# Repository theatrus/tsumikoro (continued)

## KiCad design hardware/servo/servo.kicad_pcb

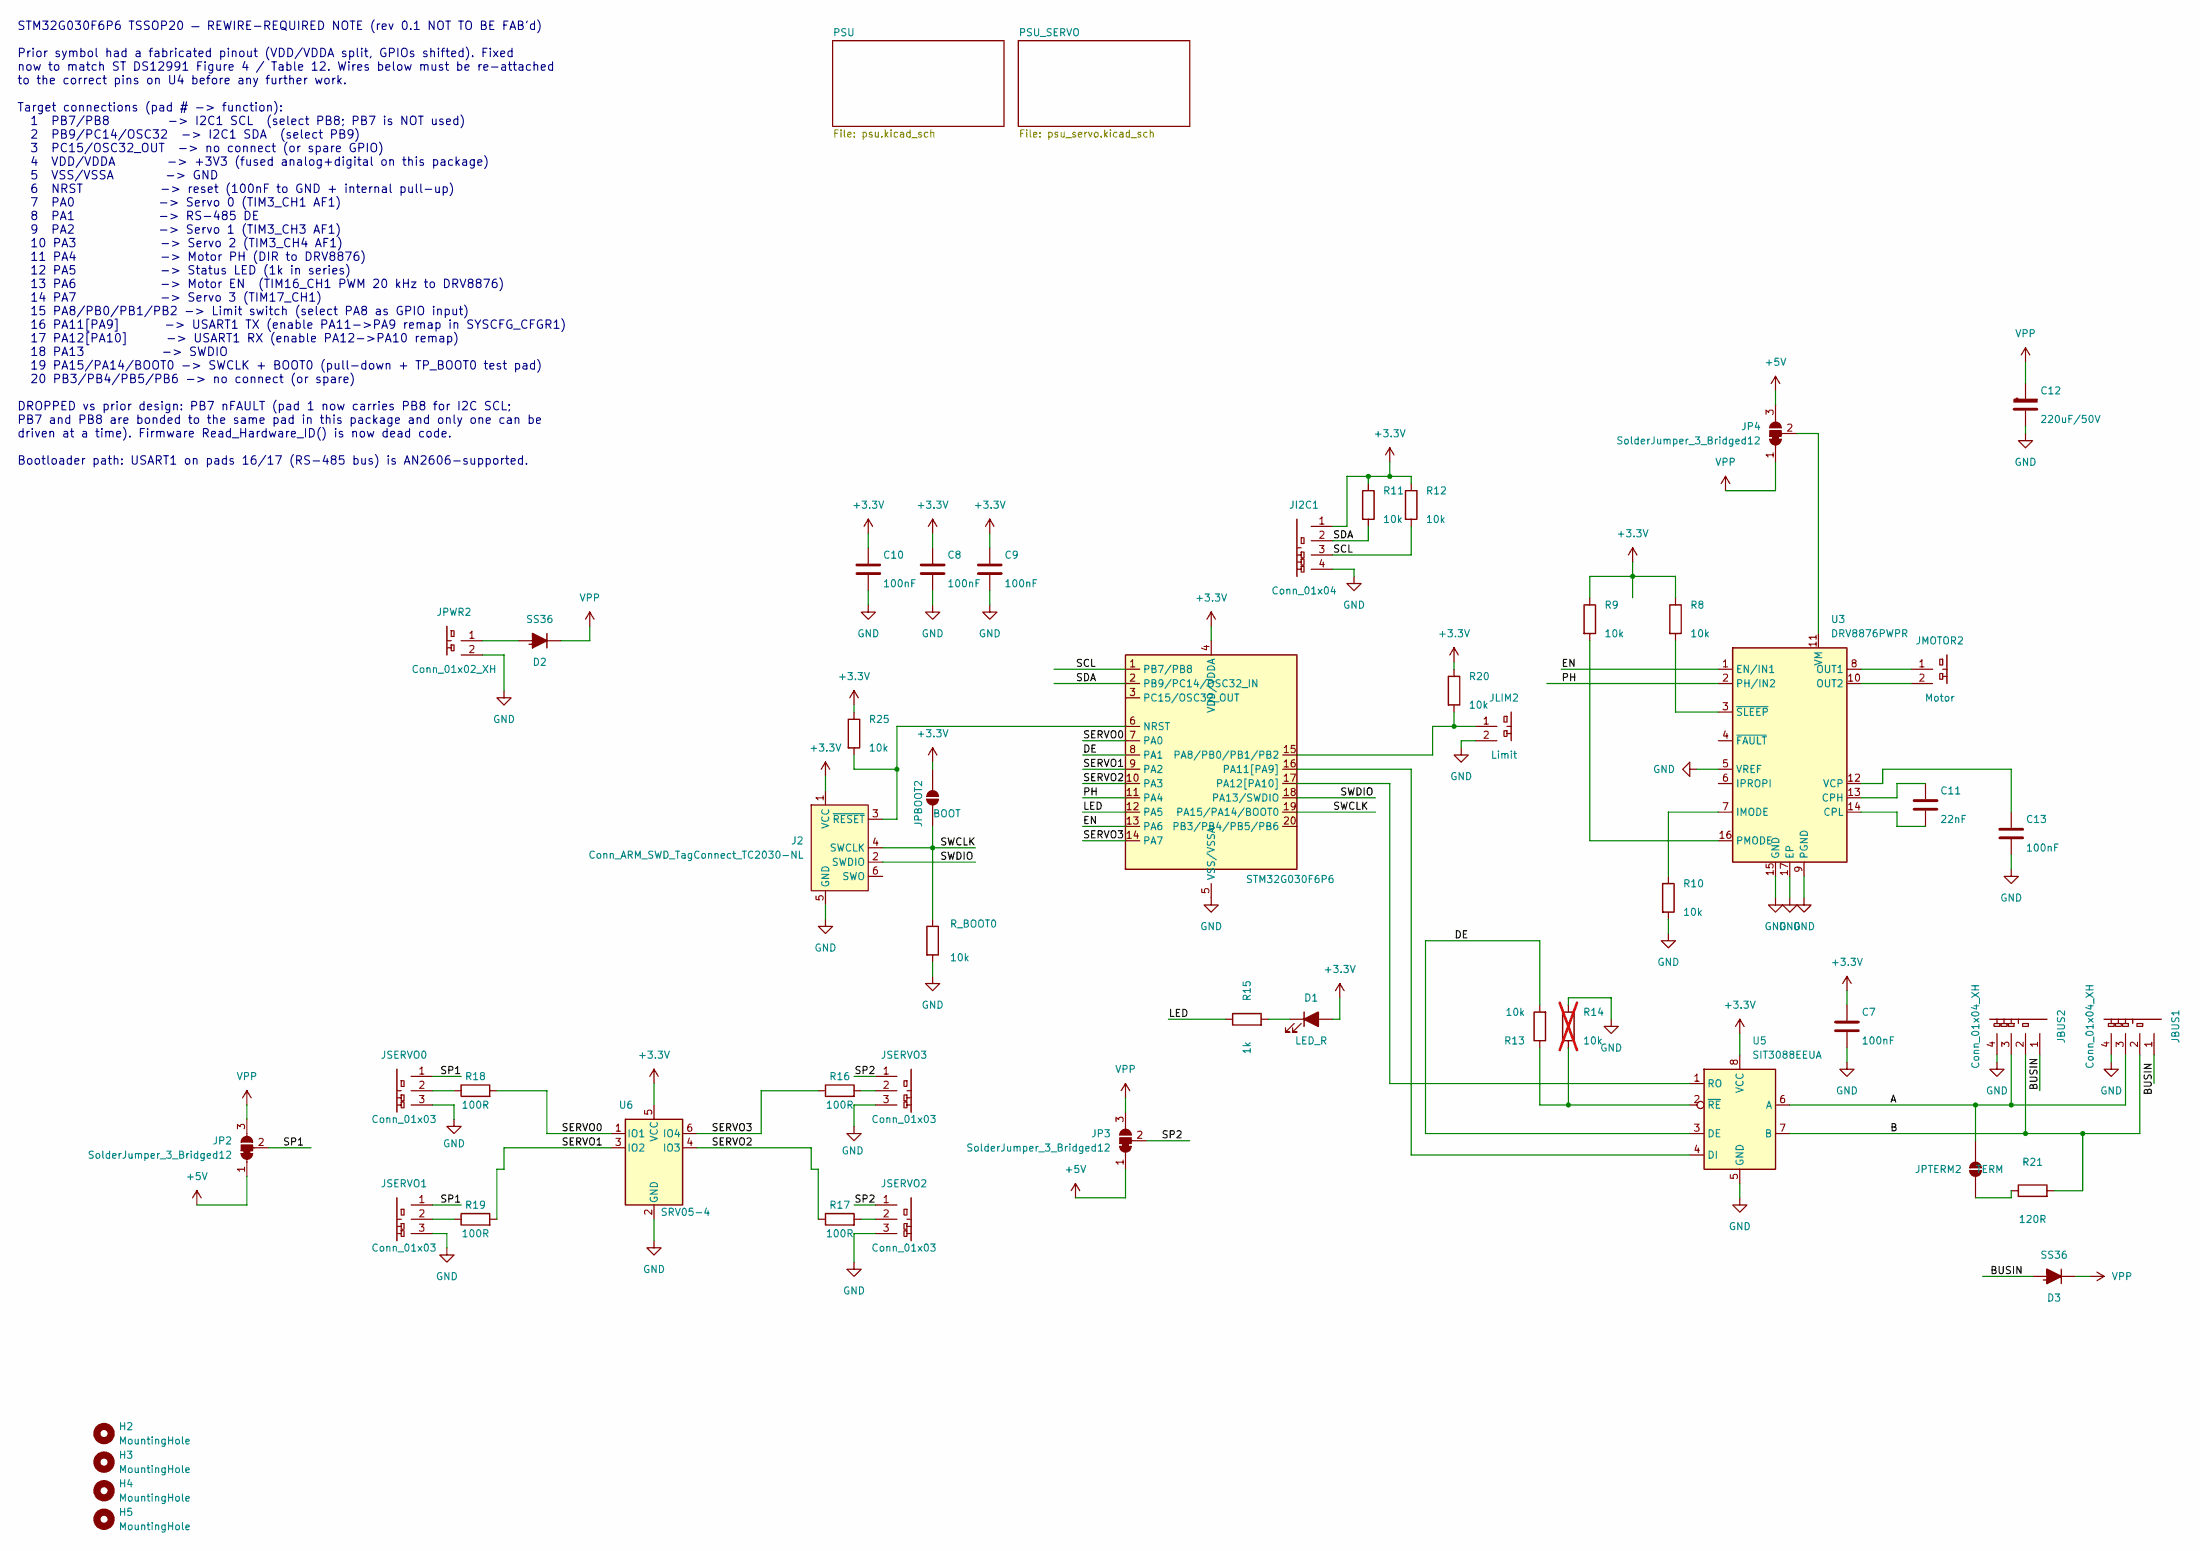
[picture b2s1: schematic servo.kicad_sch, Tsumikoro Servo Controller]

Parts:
C7, C8, C9, C10, C13: 100nF; C_0402_1005Metric; MPN CL05B104KB54PNC; LCSC C307331
C11: 22nF; C_0402_1005Metric; MPN 0402B223K500NT; LCSC C1532
C12: 220uF/50V; CP_Elec_10x10.5; MPN RVT1H221M1010; LCSC C72499
D1: LED_R; LED_0603_1608Metric; MPN KT-0603R; LCSC C2286
D2, D3: SS36; D_SMA; MPN SS36; LCSC C7420367
H2, H3, H4, H5: MountingHole; MountingHole_3.2mm_M3_Pad_TopBottom
J2: Conn_ARM_SWD_TagConnect_TC2030-NL; Tag-Connect_TC2030-IDC-NL_2x03_P1.27mm_Vertical
JBUS1, JBUS2: Conn_01x04_XH; JST_XH_S4B-XH-A_1x04_P2.50mm_Horizontal; MPN S4B-XH-A(LF)(SN); LCSC C157925
JI2C1: Conn_01x04; JST_PH_B4B-PH-K_1x04_P2.00mm_Vertical; MPN B4B-PH-K-S(LF)(SN); LCSC C131334
JLIM2: Limit; JST_PH_B2B-PH-K_1x02_P2.00mm_Vertical; MPN B2B-PH-K-S(LF)(SN); LCSC C131337
JMOTOR2: Motor; JST_PH_B2B-PH-K_1x02_P2.00mm_Vertical; MPN B2B-PH-K-S(LF)(SN); LCSC C131337
JP2, JP3, JP4: SolderJumper_3_Bridged12; SolderJumper-3_P1.3mm_Bridged12_RoundedPad1.0x1.5mm
JPBOOT2: BOOT; SolderJumper-2_P1.3mm_Open_Pad1.0x1.5mm
JPTERM2: TERM
JPWR2: Conn_01x02_XH; JST_XH_S2B-XH-A_1x02_P2.50mm_Horizontal; MPN S2B-XH-A(LF)(SN); LCSC C157931
JSERVO0, JSERVO1, JSERVO2, JSERVO3: Conn_01x03; JST_PH_B3B-PH-K_1x03_P2.00mm_Vertical; MPN B3B-PH-K-S(LF)(SN); LCSC C131339
R8, R9, R10, R11, R12, R13, R20, R25: 10k; R_0402_1005Metric; MPN 0402WGF1002TCE; LCSC C25744
R14: 10k; R_0402_1005Metric; MPN 0402WGF1002TCE; LCSC C25744; not fitted
R15: 1k; R_0402_1005Metric; MPN 0402WGF1001TCE; LCSC C11702
R16, R17, R18, R19: 100R; R_0402_1005Metric; MPN 0402WGF1000TCE; LCSC C25076
R21: 120R; R_1206_3216Metric; MPN RC1206FR-07120RL; LCSC C114928
R_BOOT0: 10k; R_0402_1005Metric; MPN 0402WGF1002TCE; LCSC C25744
U3: DRV8876PWPR; HTSSOP-16-1EP_4.4x5mm_P0.65mm_EP3.4x5mm; MPN DRV8876PWPR; LCSC C575551
U4: STM32G030F6P6; TSSOP-20_4.4x6.5mm_P0.65mm; MPN STM32G030F6P6TR; LCSC C529330
U5: SIT3088EEUA; MSOP-8_3x3mm_P0.65mm; MPN SIT3088EEUA; LCSC C2922535
U6: SRV05-4; SOT-23-6; MPN SRV05-4; LCSC C558418

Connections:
+3.3V: C7.1, C8.1, C9.1, C10.1, D1.2 (A), J2.1 (VCC), JI2C1.1, JPBOOT2.2 (B), R8.1, R9.1, R11.1, R12.1, R20.1, R25.1, U4.4 (VDD/VDDA), U5.8 (VCC), U6.5 (VCC); also elsewhere on the board
+5V: JP2.1 (A), JP3.1 (A), JP4.3 (B); also elsewhere on the board
/<NO NET>: D3.2 (A), JBUS1.1, JBUS2.1
/A: JBUS1.3, JBUS2.3, JPTERM2.2 (B), U5.6 (A)
/B: JBUS1.2, JBUS2.2, R21.2, U5.7 (B)
/DE: R13.2, U4.8 (PA1), U5.3 (DE)
/EN: U3.1 (EN/IN1), U4.13 (PA6)
/LED: R15.1, U4.12 (PA5)
/PH: U3.2 (PH/IN2), U4.11 (PA4)
/SCL: JI2C1.3, R12.2, U4.1 (PB7/PB8)
/SDA: JI2C1.2, R11.2, U4.2 (PB9/PC14/OSC32_IN)
/SERVO0: R18.2, U4.7 (PA0), U6.1 (IO1)
/SERVO1: R19.2, U4.9 (PA2), U6.3 (IO2)
/SERVO2: R17.1, U4.10 (PA3), U6.4 (IO3)
/SERVO3: R16.1, U4.14 (PA7), U6.6 (IO4)
/SP1: JP2.2 (C), JSERVO0.1, JSERVO1.1
/SP2: JP3.2 (C), JSERVO2.1, JSERVO3.1
/SWCLK: J2.4 (SWCLK), JPBOOT2.1 (A), R_BOOT0.1, U4.19 (PA15/PA14/BOOT0)
/SWDIO: J2.2 (SWDIO), U4.18 (PA13/SWDIO)
GND: C7.2, C8.2, C9.2, C10.2, C12.2, C13.2, J2.5 (GND), JBUS1.4, JBUS2.4, JI2C1.4, JLIM2.2, JPWR2.2, JSERVO0.3, JSERVO1.3, JSERVO2.3, JSERVO3.3, R10.2, R14.1, R_BOOT0.2, U3.5 (VREF), U3.9 (PGND), U3.15 (GND), U3.17 (EP), U4.5 (VSS/VSSA), U5.5 (GND), U6.2 (GND); also elsewhere on the board
unnamed: D1.1 (K), R15.2
unnamed: D2.2 (A), JPWR2.1
unnamed: J2.3 (~RESET), R25.2, U4.6 (NRST)
unnamed: JLIM2.1, R20.2, U4.15 (PA8/PB0/PB1/PB2)
unnamed: JMOTOR2.1, U3.8 (OUT1)
unnamed: JMOTOR2.2, U3.10 (OUT2)
unnamed: JP4.2 (C), U3.11 (VM)
unnamed: JPTERM2.1 (A), R21.1
unnamed: JSERVO0.2, R18.1
unnamed: JSERVO1.2, R19.1
unnamed: JSERVO2.2, R17.2
unnamed: JSERVO3.2, R16.2
unnamed: C11.1, U3.13 (CPH)
unnamed: C11.2, U3.14 (CPL)
unnamed: R10.1, U3.7 (IMODE)
unnamed: R9.2, U3.16 (PMODE)
unnamed: C13.1, U3.12 (VCP)
unnamed: R8.2, U3.3 (~SLEEP)
unnamed: U4.16 (PA11[PA9]), U5.4 (DI)
unnamed: U4.17 (PA12[PA10]), U5.1 (RO)
unnamed: R13.1, R14.2, U5.2 (~RE)
VPP: C12.1, D2.1 (K), D3.1 (K), JP2.3 (B), JP3.3 (B), JP4.1 (A); also elsewhere on the board

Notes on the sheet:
STM32G030F6P6 TSSOP20 — REWIRE-REQUIRED NOTE (rev 0.1 NOT TO BE FAB'd) Prior symbol had a fabricated pinout (VDD/VDDA split, GPIOs shifted). Fixed now to match ST DS12991 Figure 4 / Table 12. Wires below must be re-attached to the correct pins on U4 before any further work. Target connections (pad 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

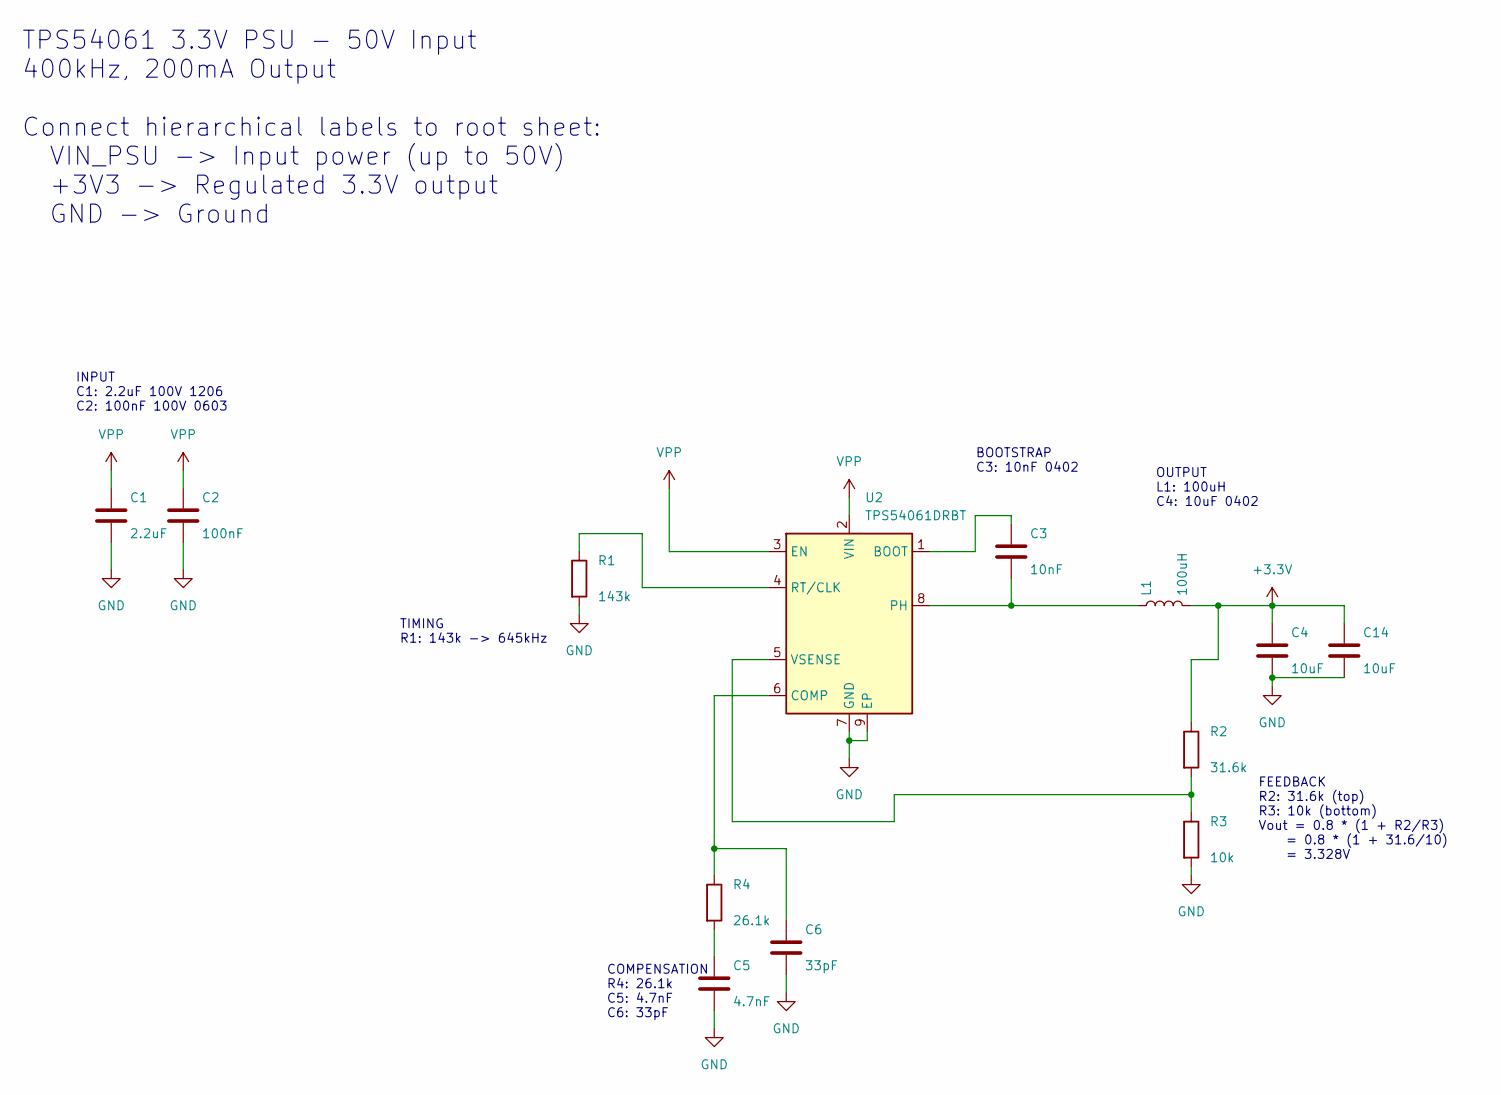
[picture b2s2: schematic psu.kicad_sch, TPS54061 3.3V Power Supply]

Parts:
C1: 2.2uF; C_1206_3216Metric; MPN CL31B225KCHSNNE; LCSC C170101
C2: 100nF; C_0603_1608Metric; MPN CC0603KRX7R0BB104; LCSC C113803
C3: 10nF; C_0402_1005Metric; MPN CL05B103KB5NNNC; LCSC C15195
C4, C14: 10uF; C_0402_1005Metric; MPN CL05A106MP5NUNC; LCSC C315248
C5: 4.7nF; C_0402_1005Metric; MPN 0402B472K500NT; LCSC C1538
C6: 33pF; C_0402_1005Metric; MPN CC0402JRNPO9BN330; LCSC C107005
L1: 100uH; L_Sunlord_SWPA4018S; MPN LVS404018-101M-N; LCSC C142135
R1: 143k; R_0402_1005Metric; MPN 0402WGF1433TCE; LCSC C82292
R2: 31.6k; R_0402_1005Metric; MPN 0402WGF3163TCE; LCSC C25777
R3: 10k; R_0402_1005Metric; MPN 0402WGF1002TCE; LCSC C25744
R4: 26.1k; R_0402_1005Metric; MPN 0402WGF2613TCE; LCSC C27003
U2: TPS54061DRBT; Texas_S-PVSON-N8; MPN TPS54061DRBT; LCSC C2070655

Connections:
+3.3V: C4.1, C14.1, L1.2, R2.1; also elsewhere on the board
GND: C1.2, C2.2, C4.2, C5.2, C6.2, C14.2, R1.2, R3.2, U2.7 (GND), U2.9 (EP); also elsewhere on the board
unnamed: C5.1, R4.2
unnamed: C3.1, U2.1 (BOOT)
unnamed: C6.1, R4.1, U2.6 (COMP)
unnamed: C3.2, L1.1, U2.8 (PH)
unnamed: R1.1, U2.4 (RT/CLK)
unnamed: R2.2, R3.1, U2.5 (VSENSE)
VPP: C1.1, C2.1, U2.2 (VIN), U2.3 (EN); also elsewhere on the board

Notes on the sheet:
TPS54061 3.3V PSU - 50V Input 400kHz, 200mA Output Connect hierarchical labels to root sheet: VIN_PSU -> Input power (up to 50V) +3V3 -> Regulated 3.3V output GND -> Ground
COMPENSATION R4: 26.1k C5: 4.7nF C6: 33pF
OUTPUT L1: 100uH C4: 10uF 0402
TIMING R1: 143k -> 645kHz
INPUT C1: 2.2uF 100V 1206 C2: 100nF 100V 0603
FEEDBACK R2: 31.6k (top) R3: 10k (bottom) Vout = 0.8 * (1 + R2/R3) = 0.8 * (1 + 31.6/10) = 3.328V
BOOTSTRAP C3: 10nF 0402

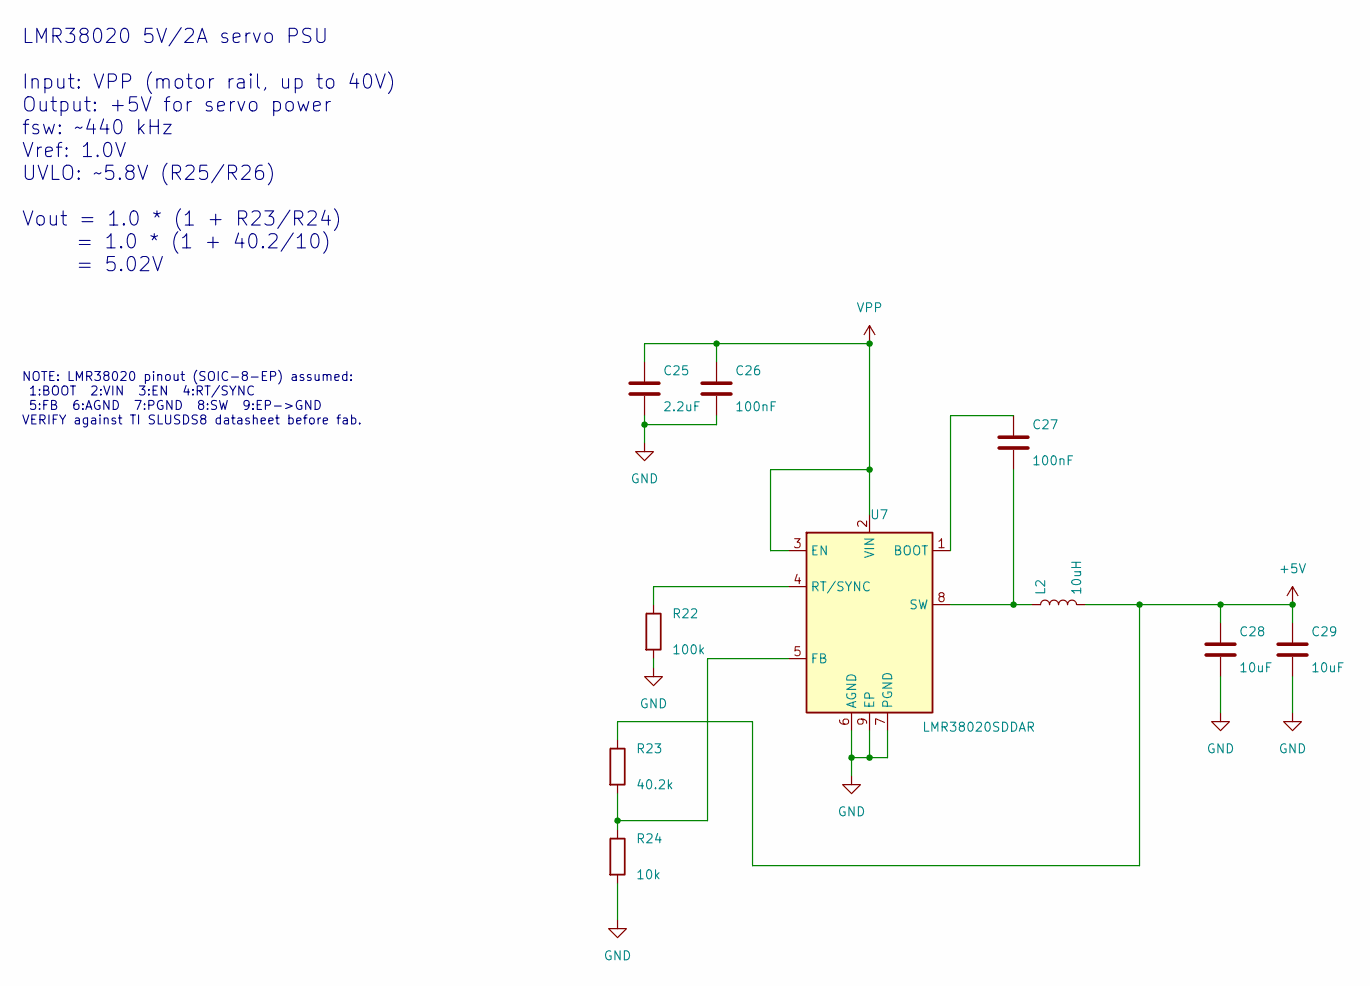
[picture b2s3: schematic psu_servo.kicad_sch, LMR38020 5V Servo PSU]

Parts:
C25: 2.2uF; C_1206_3216Metric; MPN CL31B225KCHSNNE; LCSC C170101
C26: 100nF; C_0603_1608Metric; MPN CC0603KRX7R0BB104; LCSC C113803
C27: 100nF; C_0402_1005Metric; MPN CL05B104KB54PNC; LCSC C307331
C28, C29: 10uF; C_0805_2012Metric; MPN CL21A106KAYNNNE; LCSC C15850
L2: 10uH; L_Changjiang_FNR4030S; MPN FNR4030S100MT; LCSC C167879
R22: 100k; R_0402_1005Metric; MPN 0402WGF1003TCE; LCSC C25741
R23: 40.2k; R_0402_1005Metric; MPN 0402WGF4022TCE; LCSC C25893
R24: 10k; R_0402_1005Metric; MPN 0402WGF1002TCE; LCSC C25744
U7: LMR38020SDDAR; SOIC-8-1EP_3.9x4.9mm_P1.27mm_EP2.29x3mm; MPN LMR38020SDDAR; LCSC C3192337

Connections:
+5V: C28.1, C29.1, L2.2, R23.1; also elsewhere on the board
GND: C25.2, C26.2, C28.2, C29.2, R22.2, R24.2, U7.6 (AGND), U7.7 (PGND), U7.9 (EP); also elsewhere on the board
unnamed: C27.1, U7.1 (BOOT)
unnamed: R23.2, R24.1, U7.5 (FB)
unnamed: R22.1, U7.4 (RT/SYNC)
unnamed: C27.2, L2.1, U7.8 (SW)
VPP: C25.1, C26.1, U7.2 (VIN), U7.3 (EN); also elsewhere on the board

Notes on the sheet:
LMR38020 5V/2A servo PSU Input: VPP (motor rail, up to 40V) Output: +5V for servo power fsw: ~440 kHz Vref: 1.0V UVLO: ~5.8V (R25/R26) Vout = 1.0 * (1 + R23/R24) = 1.0 * (1 + 40.2/10) = 5.02V
NOTE: LMR38020 pinout (SOIC-8-EP) assumed: 1:BOOT 2:VIN 3:EN 4:RT/SYNC 5:FB 6:AGND 7:PGND 8:SW 9:EP->GND VERIFY against TI SLUSDS8 datasheet before fab.

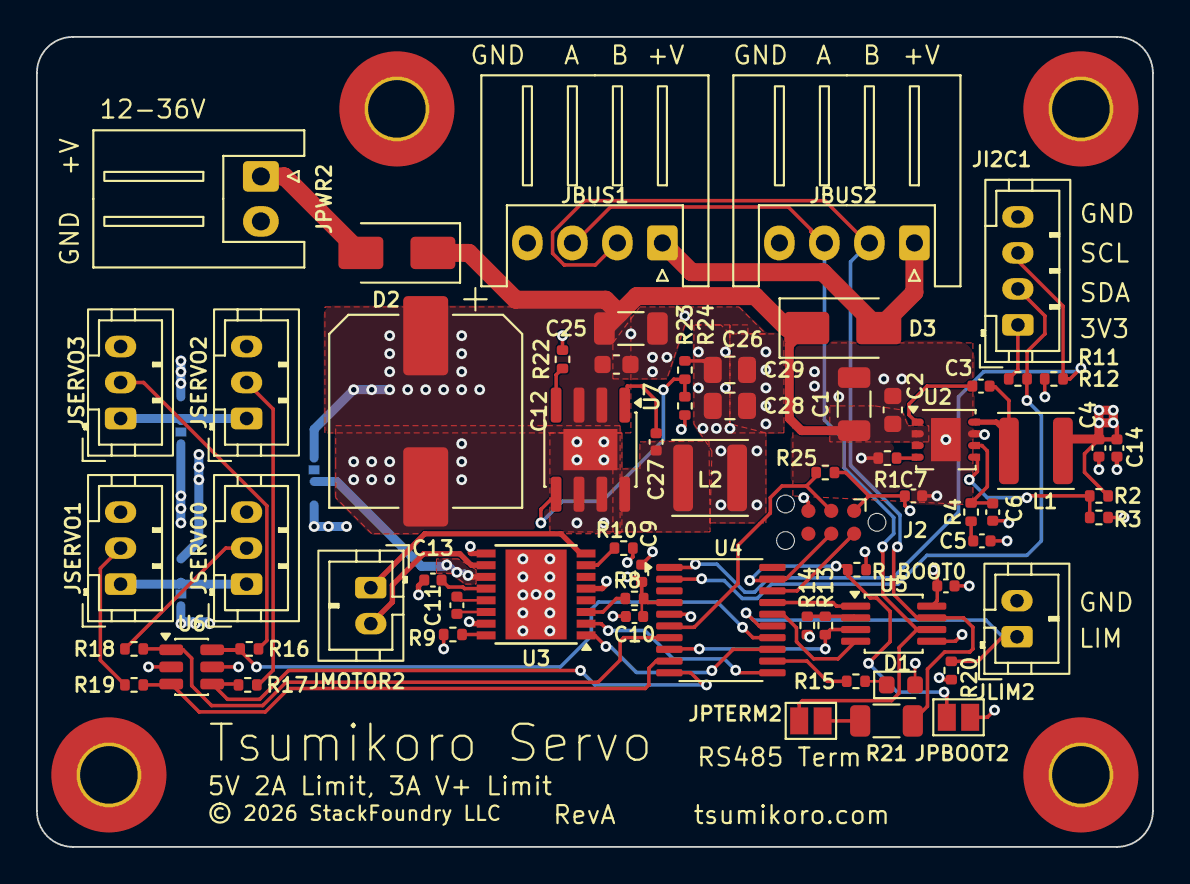
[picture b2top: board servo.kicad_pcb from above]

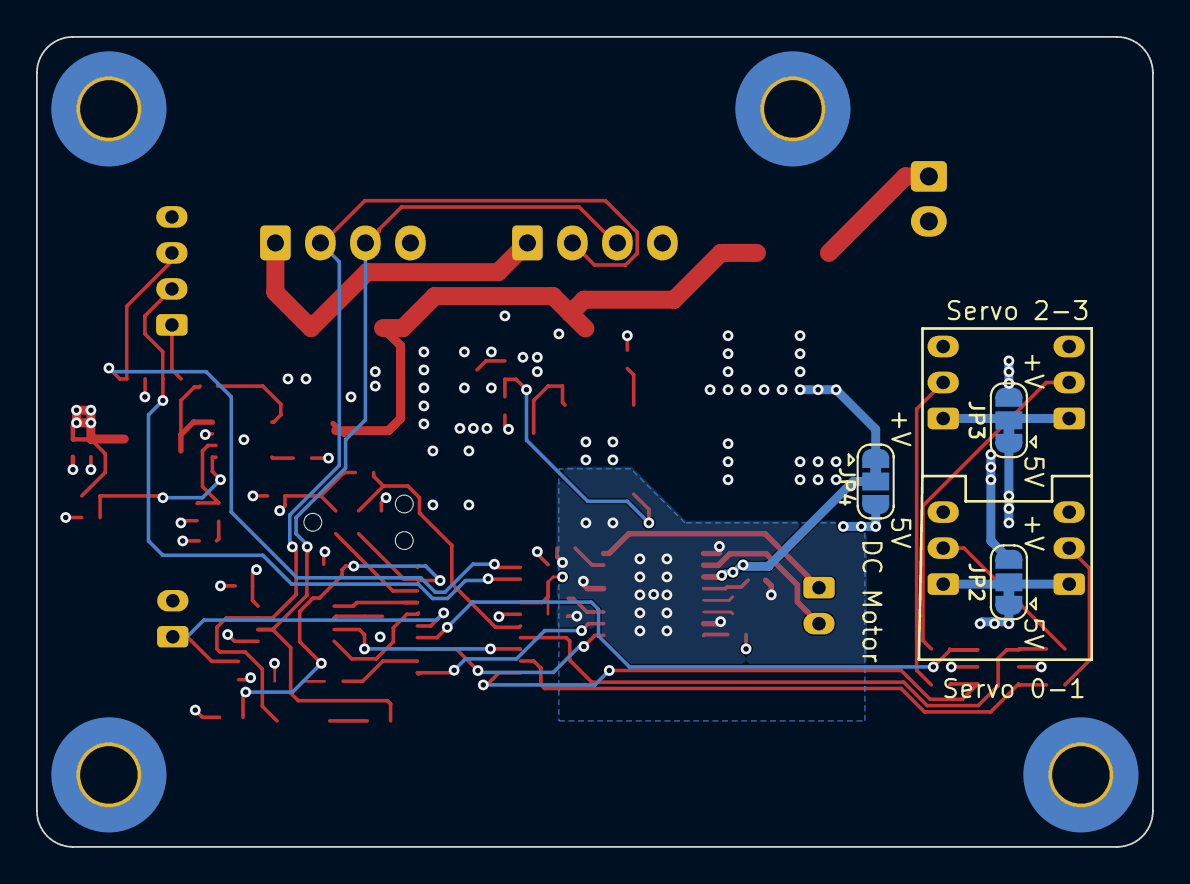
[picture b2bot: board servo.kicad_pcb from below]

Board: 4 copper layers, 62.0 x 45.0 mm, 73 parts (3 on the bottom side), 52 nets.

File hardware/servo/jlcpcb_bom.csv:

"Item","Designator","Comment","Footprint","Qty","LCSC Part #","MPN","Manufacturer"
"1","C1,C25","2.2uF","Capacitor_SMD:C_1206_3216Metric","2","C170101","CL31B225KCHSNNE","Samsung"
"2","C2,C26","100nF","Capacitor_SMD:C_0603_1608Metric","2","C113803","CC0603KRX7R0BB104","Yageo"
"3","C3","10nF","Capacitor_SMD:C_0402_1005Metric","1","C15195","CL05B103KB5NNNC","Samsung"
"4","C4,C14","10uF","Capacitor_SMD:C_0402_1005Metric","2","C315248","CL05A106MP5NUNC","Samsung"
"5","C5","4.7nF","Capacitor_SMD:C_0402_1005Metric","1","C1538","0402B472K500NT","FH"
"6","C6","33pF","Capacitor_SMD:C_0402_1005Metric","1","C107005","CC0402JRNPO9BN330","Yageo"
"7","C7-C10,C13,C27","100nF","Capacitor_SMD:C_0402_1005Metric","6","C307331","CL05B104KB54PNC","Samsung"
"8","C11","22nF","Capacitor_SMD:C_0402_1005Metric","1","C1532","0402B223K500NT","FH"
"9","C12","220uF/50V","Capacitor_SMD:CP_Elec_10x10.5","1","C72499","RVT1H221M1010","Lelon"
"10","C28,C29","10uF","Capacitor_SMD:C_0805_2012Metric","2","C15850","CL21A106KAYNNNE","Samsung"
"11","D1","LED_R","LED_SMD:LED_0603_1608Metric","1","C2286","KT-0603R","Hubei KENTO Elec"
"12","D2,D3","SS36","Diode_SMD:D_SMA","2","C7420367","SS36","Multiple"
"13","JBUS1,JBUS2","Conn_01x04_XH","Connector_JST:JST_XH_S4B-XH-A_1x04_P2.50mm_Horizontal","2","C157925","S4B-XH-A(LF)(SN)","JST"
"14","JI2C1","Conn_01x04","Connector_JST:JST_PH_B4B-PH-K_1x04_P2.00mm_Vertical","1","C131334","B4B-PH-K-S(LF)(SN)","JST"
"15","JLIM2","Limit","Connector_JST:JST_PH_B2B-PH-K_1x02_P2.00mm_Vertical","1","C131337","B2B-PH-K-S(LF)(SN)","JST"
"16","JMOTOR2","Motor","Connector_JST:JST_PH_B2B-PH-K_1x02_P2.00mm_Vertical","1","C131337","B2B-PH-K-S(LF)(SN)","JST"
"17","JPWR2","Conn_01x02_XH","Connector_JST:JST_XH_S2B-XH-A_1x02_P2.50mm_Horizontal","1","C157931","S2B-XH-A(LF)(SN)","JST"
"18","JSERVO0-JSERVO3","Conn_01x03","Connector_JST:JST_PH_B3B-PH-K_1x03_P2.00mm_Vertical","4","C131339","B3B-PH-K-S(LF)(SN)","JST"
"19","L1","100uH","Inductor_SMD:L_Sunlord_SWPA4018S","1","C142135","LVS404018-101M-N","BOURNS/LVS"
"20","L2","10uH","Inductor_SMD:L_Changjiang_FNR4030S","1","C167879","FNR4030S100MT","Sunlord"
"21","R1","143k","Resistor_SMD:R_0402_1005Metric","1","C82292","0402WGF1433TCE","UNI-ROYAL"
"22","R2","31.6k","Resistor_SMD:R_0402_1005Metric","1","C25777","0402WGF3163TCE","UNI-ROYAL"
"23","R3,R8-R13,R20,R24,R25,R_BOOT0","10k","Resistor_SMD:R_0402_1005Metric","11","C25744","0402WGF1002TCE","UNI-ROYAL"
"24","R4","26.1k","Resistor_SMD:R_0402_1005Metric","1","C27003","0402WGF2613TCE","UNI-ROYAL"
"25","R15","1k","Resistor_SMD:R_0402_1005Metric","1","C11702","0402WGF1001TCE","UNI-ROYAL"
"26","R16-R19","100R","Resistor_SMD:R_0402_1005Metric","4","C25076","0402WGF1000TCE","UNI-ROYAL"
"27","R21","120R","Resistor_SMD:R_1206_3216Metric","1","C114928","RC1206FR-07120RL","Yageo"
"28","R22","100k","Resistor_SMD:R_0402_1005Metric","1","C25741","0402WGF1003TCE","UNI-ROYAL"
"29","R23","40.2k","Resistor_SMD:R_0402_1005Metric","1","C25893","0402WGF4022TCE","UNI-ROYAL"
"30","U2","TPS54061DRBT","Package_SON:Texas_S-PVSON-N8","1","C2070655","TPS54061DRBT",""
"31","U3","DRV8876PWPR","Package_SO:HTSSOP-16-1EP_4.4x5mm_P0.65mm_EP3.4x5mm","1","C575551","DRV8876PWPR",""
"32","U4","STM32G030F6P6","Package_SO:TSSOP-20_4.4x6.5mm_P0.65mm","1","C529330","STM32G030F6P6TR",""
"33","U5","SIT3088EEUA","Package_SO:MSOP-8_3x3mm_P0.65mm","1","C2922535","SIT3088EEUA",""
"34","U6","SRV05-4","Package_TO_SOT_SMD:SOT-23-6","1","C558418","SRV05-4","Littelfuse"
"35","U7","LMR38020SDDAR","Package_SO:SOIC-8-1EP_3.9x4.9mm_P1.27mm_EP2.29x3mm","1","C3192337","LMR38020SDDAR","Texas Instruments"

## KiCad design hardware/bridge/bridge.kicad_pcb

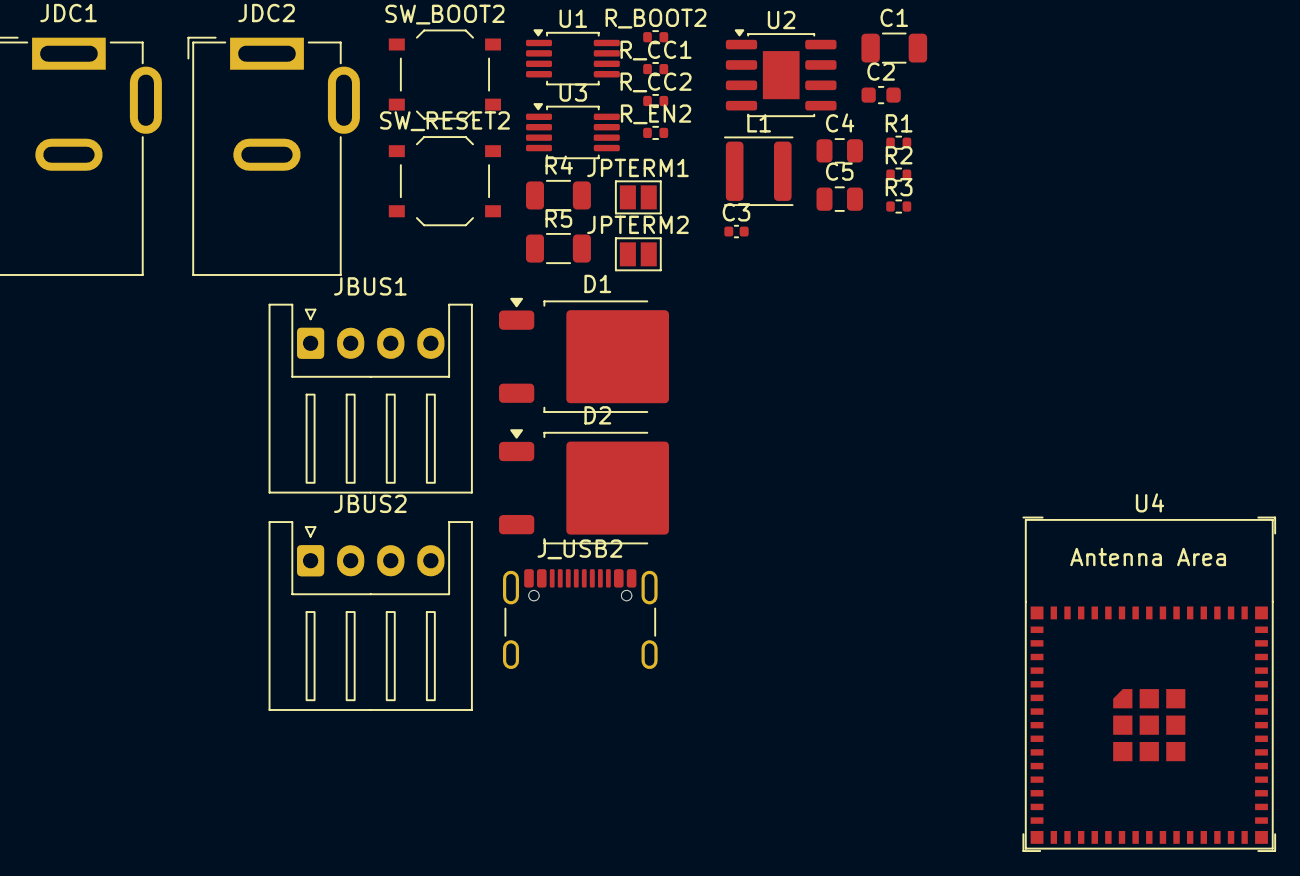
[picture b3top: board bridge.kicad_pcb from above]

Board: 4 copper layers, 30 parts (0 on the bottom side), 3 nets, no tracks yet.

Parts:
C1: 2.2uF; C_1206_3216Metric
C2: 100nF; C_0603_1608Metric
C3: 100nF; C_0402_1005Metric
C4, C5: 10uF; C_0805_2012Metric
D1, D2: MBRD10200; TO-252-2
JBUS1, JBUS2: Conn_01x04_XH; JST_XH_S4B-XH-A_1x04_P2.50mm_Horizontal
JDC1, JDC2: DC-005 2.0mm; BarrelJack_GCT_DCJ200-10-A_Horizontal
JPTERM1: TERM1; SolderJumper-2_P1.3mm_Open_Pad1.0x1.5mm
JPTERM2: TERM2; SolderJumper-2_P1.3mm_Open_Pad1.0x1.5mm
J_USB2: USB-TYPE-C-019; USB_C_Receptacle_GCT_USB4105-xx-A_16P_TopMnt_Horizontal
L1: 10uH; L_Changjiang_FNR4030S
R1: 100k; R_0402_1005Metric
R2: 22k; R_0402_1005Metric
R3: 10k; R_0402_1005Metric
R4, R5: 120R; R_1206_3216Metric
R_BOOT2: 10k; R_0402_1005Metric
R_CC1, R_CC2: 5.1k; R_0402_1005Metric
R_EN2: 10k; R_0402_1005Metric
SW_BOOT2: BOOT; SW_Push_1P1T_XKB_TS-1187A
SW_RESET2: RESET; SW_Push_1P1T_XKB_TS-1187A
U1, U3: SIT3088EEUA; MSOP-8_3x3mm_P0.65mm
U2: LMR38020SDDAR; SOIC-8-1EP_3.9x4.9mm_P1.27mm_EP2.29x3mm
U4: ESP32-S3-MINI-1-N8; ESP32-S3-MINI-1

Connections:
unnamed: J_USB2.A1 (GND), J_USB2.A12 (GND), J_USB2.B1 (GND), J_USB2.B12 (GND)
unnamed: J_USB2.A4 (VBUS), J_USB2.A9 (VBUS), J_USB2.B4 (VBUS), J_USB2.B9 (VBUS)
unnamed: U4.1 (GND), U4.2 (GND), U4.42 (GND), U4.43 (GND), U4.46 (GND), U4.47 (GND), U4.48 (GND), U4.49 (GND), U4.50 (GND), U4.51 (GND), U4.52 (GND), U4.53 (GND), U4.54 (GND), U4.55 (GND), U4.56 (GND), U4.57 (GND), U4.58 (GND), U4.59 (GND), U4.60 (GND), U4.61 (GND), U4.62 (GND), U4.63 (GND), U4.64 (GND), U4.65 (GND)

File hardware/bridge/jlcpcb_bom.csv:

"Item","Designator","Comment","Footprint","Qty","LCSC Part #","MPN","Manufacturer"
"1","C1","2.2uF","Capacitor_SMD:C_1206_3216Metric","1","C170101","CL31B225KCHSNNE","Samsung"
"2","C2","100nF","Capacitor_SMD:C_0603_1608Metric","1","C113803","CC0603KRX7R0BB104","Yageo"
"3","C3","100nF","Capacitor_SMD:C_0402_1005Metric","1","C1525","CL05B104KO5NNNC","Samsung"
"4","C4,C5","10uF","Capacitor_SMD:C_0805_2012Metric","2","C15850","CL21A106KAYNNNE","Samsung"
"5","D1,D2","MBRD10200","Package_TO_SOT_SMD:TO-252-2","2","C260297","MBRD10200","onsemi"
"6","JBUS1,JBUS2","Conn_01x04_XH","Connector_JST:JST_XH_S4B-XH-A_1x04_P2.50mm_Horizontal","2","C157925","S4B-XH-A(LF)(SN)","JST"
"7","JDC1,JDC2","DC-005 2.0mm","Connector_BarrelJack:BarrelJack_CUI_PJ-063AH_Horizontal","2","C2880546","DC-005K-5A-2.0","XKB Connectivity"
"8","JPTERM1","TERM1","Jumper:SolderJumper-2_P1.3mm_Open_Pad1.0x1.5mm","1","","",""
"9","JPTERM2","TERM2","Jumper:SolderJumper-2_P1.3mm_Open_Pad1.0x1.5mm","1","","",""
"10","J_ESP_L?","ESP32-L 1x19","Connector_PinHeader_2.54mm:PinSocket_1x19_P2.54mm_Vertical","1","","",""
"11","J_ESP_R?","ESP32-R 1x19","Connector_PinHeader_2.54mm:PinSocket_1x19_P2.54mm_Vertical","1","","",""
"12","L1","10uH","Inductor_SMD:L_Changjiang_FNR4030S","1","C167879","FNR4030S100MT","Sunlord"
"13","R1","100k","Resistor_SMD:R_0402_1005Metric","1","C25741","0402WGF1003TCE","UNI-ROYAL"
"14","R2","22k","Resistor_SMD:R_0402_1005Metric","1","C25768","0402WGF2202TCE","UNI-ROYAL"
"15","R3","10k","Resistor_SMD:R_0402_1005Metric","1","C25744","0402WGF1002TCE","UNI-ROYAL"
"16","R4,R5","120R","Resistor_SMD:R_1206_3216Metric","2","C114928","RC1206FR-07120RL","Yageo"
"17","U1,U3","SIT3088EEUA","Package_SO:MSOP-8_3x3mm_P0.65mm","2","C2922535","SIT3088EEUA","3PEAK"
"18","U2","LMR38020SDDAR","Package_SO:SOIC-8-1EP_3.9x4.9mm_P1.27mm_EP2.29x3mm","1","C3192337","LMR38020SDDAR","Texas Instruments"

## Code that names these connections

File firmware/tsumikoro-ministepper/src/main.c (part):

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 * the `PIN_*` defines below MUST stay in sync with that document.
 *
 * Peripheral allocation:
 *   USART2 (PA2/PA3)          - RS-485 bus @ 1 Mbaud
 *   SPI1   (PA5/PA6/PA7)      - shared SPI to both TMC2130s
 *   TIM1_CH1 (PA8)            - STEP1 pulse generator
 *   TIM2_CH1 (PA0)            - STEP2 pulse generator
 *   I2C1   (PB6/PB7)          - expansion bus (AF6)
 *
 * USART2 is used instead of USART1 to avoid the PA11/PA12 vs PA9/PA10
 * shared-pad trap that hit the servo firmware on STM32G030F6P6 — on
 * the G071 UFQFPN-28 PA2/PA3 are dedicated pins so no SYSCFG remap is
 * needed.
 */

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#define PIN_TMC1_CS_PORT        GPIOA
#define PIN_TMC1_CS             GPIO_PIN_4   /* pin 10 - CS1 */
#define PIN_TMC1_STEP_PORT      GPIOA
#define PIN_TMC1_STEP           GPIO_PIN_8   /* pin 16 - STEP1 (TIM1_CH1, AF2) */
#define PIN_TMC1_DIR_PORT       GPIOA
#define PIN_TMC1_DIR            GPIO_PIN_15  /* pin 22 - DIR1 */
#define PIN_TMC1_DIAG_PORT      GPIOB
#define PIN_TMC1_DIAG           GPIO_PIN_1   /* pin 15 - DIAG1 (open-drain + 47k pull-up) */

/* TMC2130 driver 2 (U3) - axis 2 */
#define PIN_TMC2_CS_PORT        GPIOA
#define PIN_TMC2_CS             GPIO_PIN_9   /* pin 19 - CS2 (was PA12, moved for USB) */
#define PIN_TMC2_STEP_PORT      GPIOA
#define PIN_TMC2_STEP           GPIO_PIN_0   /* pin 6  - STEP2 (TIM2_CH1, AF2) */
#define PIN_TMC2_DIR_PORT       GPIOC        /* <-- PC6 (pin 17); PB2 is not bonded out on UFQFPN28 */
#define PIN_TMC2_DIR            GPIO_PIN_6   /* pin 17 - DIR2 */
#define PIN_TMC2_DIAG_PORT      GPIOB
#define PIN_TMC2_DIAG           GPIO_PIN_4   /* pin 24 - DIAG2 */

/* Shared DRV_ENN for both TMC2130s (active-low enable) */
#define PIN_DRV_ENN_PORT        GPIOB
#define PIN_DRV_ENN             GPIO_PIN_2   /* pin 17 - active low enable (was PA11, moved for USB) */

/* Per-axis limit / home switches */
#define PIN_LIMIT1_PORT         GPIOB
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#define PIN_I2C_SCL             GPIO_PIN_6   /* pin 26 - I2C1 SCL (AF6) */
#define PIN_I2C_SDA             GPIO_PIN_7   /* pin 27 - I2C1 SDA (AF6) */

/* USB (PA11=D-, PA12=D+ on UFQFPN-32 pins 22/23) — handled by USB peripheral, not GPIO */
/* Spares on UFQFPN32: PB9 (pin 1), PC14 (pin 2), PC15 (pin 3), PA10 (pin 21), PB8 (pin 32) */

/* ===== Task sizes ======================================================== */

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{
    __HAL_RCC_GPIOA_CLK_ENABLE();
    __HAL_RCC_GPIOB_CLK_ENABLE();
    __HAL_RCC_GPIOC_CLK_ENABLE();   /* PC6 = DIR2 */

    GPIO_InitTypeDef gpio = {0};

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    gpio.Speed = GPIO_SPEED_FREQ_LOW;
    HAL_GPIO_Init(PIN_LED_PORT, &gpio);

    /* USART2 AF1 on PA2/PA3 (pins 6/7) */
    gpio.Pin = PIN_UART_TX | PIN_UART_RX;
    gpio.Mode = GPIO_MODE_AF_PP;
    gpio.Pull = GPIO_PULLUP;
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    gpio.Alternate = GPIO_AF1_USART2;
    HAL_GPIO_Init(PIN_UART_PORT, &gpio);

    /* RS-485 DE on PA1 - the HAL module manages this pin explicitly */
    gpio.Pin = PIN_DE;
    gpio.Mode = GPIO_MODE_OUTPUT_PP;
    gpio.Pull = GPIO_NOPULL;
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    HAL_GPIO_Init(PIN_DE_PORT, &gpio);
    HAL_GPIO_WritePin(PIN_DE_PORT, PIN_DE, GPIO_PIN_RESET);  /* start in RX */

    /* TMC1 CS (PA4), TMC2 CS (PA12), DRV_ENN (PA11), DIR1 (PA15) — all GPIO outputs.
     * Hold CS high (inactive) and DRV_ENN high (outputs disabled) at boot. */
    gpio.Pin = PIN_TMC1_CS | PIN_TMC2_CS | PIN_DRV_ENN;
    gpio.Mode = GPIO_MODE_OUTPUT_PP;
    gpio.Pull = GPIO_NOPULL;
    gpio.Speed = GPIO_SPEED_FREQ_MEDIUM;
    HAL_GPIO_Init(GPIOA, &gpio);
    HAL_GPIO_WritePin(GPIOA, PIN_TMC1_CS | PIN_TMC2_CS, GPIO_PIN_SET);
    HAL_GPIO_WritePin(PIN_DRV_ENN_PORT, PIN_DRV_ENN, GPIO_PIN_SET);  /* drivers off */

    gpio.Pin = PIN_TMC1_DIR;
    HAL_GPIO_Init(PIN_TMC1_DIR_PORT, &gpio);
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    gpio.Pin = PIN_LIMIT2;
    HAL_GPIO_Init(PIN_LIMIT2_PORT, &gpio);

    /* STEP1 (PA8) will be configured as TIM1_CH1 AF2 by Stepper_Init.
     * STEP2 (PA0) will be configured as TIM2_CH1 AF2 by Stepper_Init.
     * SPI1 (PA5/6/7) will be configured when the SPI driver is added. */
}

static void UART_Init(void)
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static void Stepper_Init(void)
{
    /* TODO:
     *  - Configure SPI1 on PA5/6/7 (AF0) for shared TMC2130 bus
     *  - Configure TIM1_CH1 (PA8) and TIM2_CH1 (PA0) for STEP pulse
     *    generation (one-pulse mode or free-running with DMA-driven ARR)
     *  - Reset TMC2130s (hold DRV_ENN, write GCONF/CHOPCONF/IHOLD_IRUN
     *    via SPI)
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
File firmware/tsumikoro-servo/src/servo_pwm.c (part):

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{
    /* Initialize servo channels with configuration
     * Pin mapping (STM32G030F6P6 TSSOP20, servo PCB rev 0.1):
     * Channel 0: PA0 - TIM3_CH1  (AF1)
     * Channel 1: PA2 - TIM3_CH3  (AF1)
     * Channel 2: PA3 - TIM3_CH4  (AF1)
     * Channel 3: PA7 - TIM17_CH1 (AF5)
     *
     * Former servo channels now reassigned for motor control / I2C / fault:
     * - PA4 (was Servo 3, TIM14_CH1) -> DRV8876 PH pin (direction)
     * - PA6 (was Servo 4, TIM16_CH1) -> DRV8876 EN pin (PWM, via TIM16_CH1)
     * - PA7 (was Servo 5)            -> now Servo 3 on this channel
     *
     * Protected / reserved pins:
     * - PA13, PA14: SWD (SWDIO, SWCLK) - DO NOT USE
     * - PA9,  PA10: USART1 for RS-485 bus (requires SYSCFG remap on TSSOP20)
     * - PA1:        RS-485 DE
     * - PA5:        Status LED
     * - PA8:        Limit switch input
     * - PB7:        DRV8876 nFAULT input (open-drain, 10k pull-up to 3V3)
     * - PB8:        I2C1_SCL (AF6)
     * - PB9:        I2C1_SDA (AF6)
     */

    memset(g_servo_channels, 0, sizeof(g_servo_channels));

    /* Channel 0: PA0 - TIM3_CH1 (AF1) */
    g_servo_channels[0].timer = TIM3;
    g_servo_channels[0].channel = LL_TIM_CHANNEL_CH1;
    g_servo_channels[0].gpio_port = GPIOA;
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    g_servo_channels[0].speed = 10;  /* 1 degree per tick */
    g_servo_channels[0].enabled = false;

    /* Channel 1: PA2 - TIM3_CH3 (AF1) */
    g_servo_channels[1].timer = TIM3;
    g_servo_channels[1].channel = LL_TIM_CHANNEL_CH3;
    g_servo_channels[1].gpio_port = GPIOA;
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    g_servo_channels[1].speed = 10;
    g_servo_channels[1].enabled = false;

    /* Channel 2: PA3 - TIM3_CH4 (AF1) */
    g_servo_channels[2].timer = TIM3;
    g_servo_channels[2].channel = LL_TIM_CHANNEL_CH4;
    g_servo_channels[2].gpio_port = GPIOA;
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    g_servo_channels[2].speed = 10;
    g_servo_channels[2].enabled = false;

    /* Channel 3: PA7 - TIM17_CH1 (AF5) */
    g_servo_channels[3].timer = TIM17;
    g_servo_channels[3].channel = LL_TIM_CHANNEL_CH1;
    g_servo_channels[3].gpio_port = GPIOA;
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    g_servo_channels[3].enabled = false;

    /* Initialize timers (unique timers only)
     * TIM16 is no longer used here - reassigned to motor_hbridge (PA6).
     * TIM14 is no longer used - PA4 is now motor DIR GPIO.
     */
    servo_pwm_init_timer(TIM3);   /* Used by channels 0, 1, 2 */
    servo_pwm_init_timer(TIM17);  /* Used by channel 3 */
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
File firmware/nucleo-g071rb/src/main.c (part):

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 * @brief NUCLEO-G071RB development board with bus protocol and TMC2130 stepper
 *
 * Development board firmware with bus protocol support and TMC2130 stepper control.
 * - LED blinks on PA5 (LD4) - can be controlled via bus
 * - Button monitored on PC13 (B1) - can be read via bus
 * - USART2 provides debug output via ST-Link VCP (115200 baud)
 * - USART1 provides bus protocol interface (1 Mbaud)
 * - SPI1 controls TMC2130 stepper driver
 *
 * NUCLEO-G071RB pin mapping:
 * - LED (LD4): PA5
 * - User Button (B1): PC13
 * - USART2 (ST-Link VCP): PA2 (TX), PA3 (RX)
 * - USART1 (Bus): PC4 (TX/D1), PC5 (RX/D0), PA1 (DE - RS-485 Driver Enable)
 * - SPI1: PB3 (SCK), PB4 (MISO), PB5 (MOSI)
 * - TMC2130: PB0 (CS), PB1 (STEP), PB2 (DIR), PA0 (EN)
 */

#include "stm32g0xx_hal.h"
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#define CMD_BUTTON_GET          0xF003      /**< Get button state */

/* Peripheral Handles */
UART_HandleTypeDef huart2;  /* Debug UART (PA2/PA3 - ST-Link VCP) */
SPI_HandleTypeDef hspi1;    /* SPI for TMC2130 */

/* Redirect printf to debug UART for bus protocol debug */
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    .dma_rx = BUS_DMA_RX,
    .dma_tx_request = DMA_REQUEST_USART1_TX,
    .dma_rx_request = DMA_REQUEST_USART1_RX,
    .de_port = BUS_DE_PORT,  /* PA1 - RS-485 Driver Enable */
    .de_pin = BUS_DE_PIN,
    .re_port = NULL,  /* Shared with DE on most transceivers */
    .re_pin = 0,
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    __HAL_RCC_GPIOB_CLK_ENABLE();
    __HAL_RCC_GPIOC_CLK_ENABLE();

    /* Configure LED pin (PA5) */
    HAL_GPIO_WritePin(LED_PORT, LED_PIN, GPIO_PIN_RESET);
    GPIO_InitStruct.Pin = LED_PIN;
    GPIO_InitStruct.Mode = GPIO_MODE_OUTPUT_PP;
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    GPIO_InitStruct.Pull = GPIO_NOPULL;
    HAL_GPIO_Init(BUTTON_PORT, &GPIO_InitStruct);

    /* Configure RS-485 Driver Enable pin (PA1) */
    HAL_GPIO_WritePin(BUS_DE_PORT, BUS_DE_PIN, GPIO_PIN_RESET);
    GPIO_InitStruct.Pin = BUS_DE_PIN;
    GPIO_InitStruct.Mode = GPIO_MODE_OUTPUT_PP;
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    GPIO_InitStruct.Alternate = GPIO_AF1_USART1;
    HAL_GPIO_Init(GPIOC, &GPIO_InitStruct);

    /* Configure SPI1 pins (PB3=SCK, PB4=MISO, PB5=MOSI) */
    GPIO_InitStruct.Pin = SPI1_SCK_PIN | SPI1_MISO_PIN | SPI1_MOSI_PIN;
    GPIO_InitStruct.Mode = GPIO_MODE_AF_PP;
    GPIO_InitStruct.Pull = GPIO_NOPULL;
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    GPIO_InitStruct.Alternate = GPIO_AF0_SPI1;
    HAL_GPIO_Init(SPI1_SCK_PORT, &GPIO_InitStruct);

    /* Configure TMC2130 CS pin (PB0) */
    HAL_GPIO_WritePin(TMC_CS_PORT, TMC_CS_PIN, GPIO_PIN_SET);
    GPIO_InitStruct.Pin = TMC_CS_PIN;
    GPIO_InitStruct.Mode = GPIO_MODE_OUTPUT_PP;
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    GPIO_InitStruct.Speed = GPIO_SPEED_FREQ_HIGH;
    HAL_GPIO_Init(TMC_CS_PORT, &GPIO_InitStruct);

    /* Configure TMC2130 STEP pin (PB1) */
    HAL_GPIO_WritePin(TMC_STEP_PORT, TMC_STEP_PIN, GPIO_PIN_RESET);
    GPIO_InitStruct.Pin = TMC_STEP_PIN;
    GPIO_InitStruct.Mode = GPIO_MODE_OUTPUT_PP;
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    GPIO_InitStruct.Speed = GPIO_SPEED_FREQ_HIGH;
    HAL_GPIO_Init(TMC_STEP_PORT, &GPIO_InitStruct);

    /* Configure TMC2130 DIR pin (PB2) */
    HAL_GPIO_WritePin(TMC_DIR_PORT, TMC_DIR_PIN, GPIO_PIN_RESET);
    GPIO_InitStruct.Pin = TMC_DIR_PIN;
    GPIO_InitStruct.Mode = GPIO_MODE_OUTPUT_PP;
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    GPIO_InitStruct.Speed = GPIO_SPEED_FREQ_HIGH;
    HAL_GPIO_Init(TMC_DIR_PORT, &GPIO_InitStruct);

    /* Configure TMC2130 EN pin (PA0) - idle high = disabled */
    HAL_GPIO_WritePin(TMC_EN_PORT, TMC_EN_PIN, GPIO_PIN_SET);
    GPIO_InitStruct.Pin = TMC_EN_PIN;
    GPIO_InitStruct.Mode = GPIO_MODE_OUTPUT_PP;
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
/**
 * @brief USART2 Initialization (Debug UART - ST-Link VCP)
 * PA2: TX, PA3: RX
 * 115200 baud, 8N1
 */
static void USART2_Init(void)
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    __HAL_RCC_USART2_CLK_ENABLE();
    __HAL_RCC_GPIOA_CLK_ENABLE();

    /* Configure GPIO pins: PA2 (TX), PA3 (RX) */
    GPIO_InitStruct.Pin = GPIO_PIN_2 | GPIO_PIN_3;
    GPIO_InitStruct.Mode = GPIO_MODE_AF_PP;
    GPIO_InitStruct.Pull = GPIO_NOPULL;
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
/**
 * @brief SPI1 Initialization
 * PB3: SCK, PB4: MISO, PB5: MOSI
 * 1 MHz, Mode 3 (CPOL=1, CPHA=1) for TMC2130
 */
static void SPI1_Init(void)
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                     "STM32G071RBT6 @ 64 MHz\r\n"
                     "128KB Flash, 36KB RAM\r\n"
                     "Bus ID: 0x10, Baud: 1 Mbaud\r\n"
                     "USART1: PC4(TX/D1), PC5(RX/D0), PA1(DE)\r\n"
                     "TMC2130 Stepper: SPI1 + Motion Control\r\n"
                     "========================================\r\n\r\n";
    HAL_UART_Transmit(&huart2, (uint8_t *)msg, strlen(msg), 1000);
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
